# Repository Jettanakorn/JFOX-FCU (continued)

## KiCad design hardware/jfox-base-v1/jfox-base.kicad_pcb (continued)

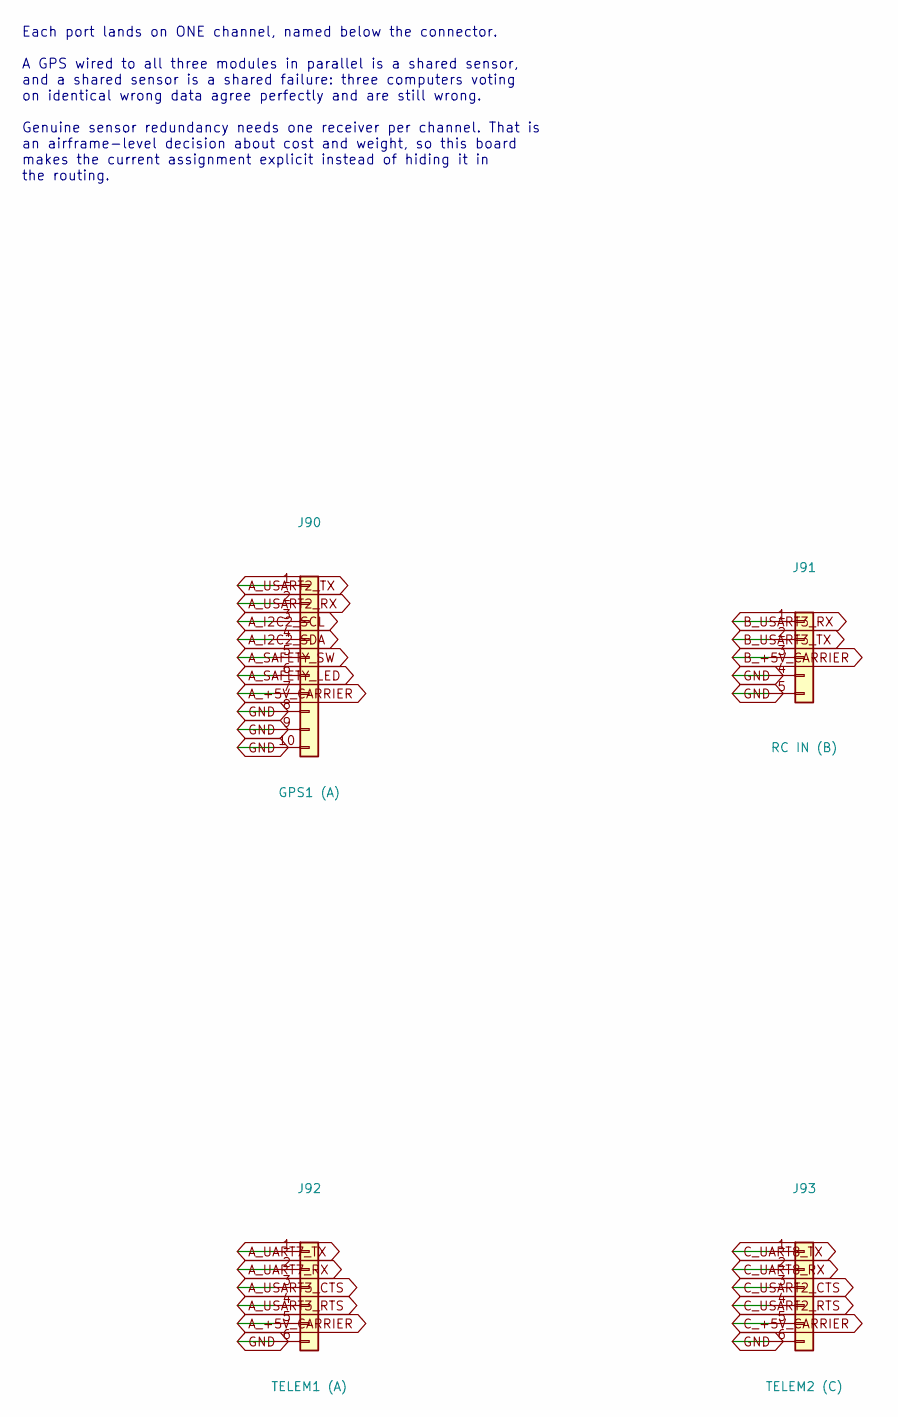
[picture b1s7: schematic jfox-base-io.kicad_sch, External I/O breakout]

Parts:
J90: GPS1 (A); JST_GH_SM10B-GHS-TB_1x10-1MP_P1.25mm_Horizontal
J91: RC IN (B); JST_GH_SM05B-GHS-TB_1x05-1MP_P1.25mm_Horizontal
J92: TELEM1 (A); JST_GH_SM06B-GHS-TB_1x06-1MP_P1.25mm_Horizontal
J93: TELEM2 (C); JST_GH_SM06B-GHS-TB_1x06-1MP_P1.25mm_Horizontal

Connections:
A_+5V_CARRIER: J90.7, J92.5; also elsewhere on the board
A_I2C2_SCL: J90.3; also elsewhere on the board
A_I2C2_SDA: J90.4; also elsewhere on the board
A_SAFETY_LED: J90.6; also elsewhere on the board
A_SAFETY_SW: J90.5; also elsewhere on the board
A_UART7_RX: J92.2; also elsewhere on the board
A_UART7_TX: J92.1; also elsewhere on the board
A_USART2_RX: J90.2; also elsewhere on the board
A_USART2_TX: J90.1; also elsewhere on the board
A_USART3_CTS: J92.3; also elsewhere on the board
A_USART3_RTS: J92.4; also elsewhere on the board
B_+5V_CARRIER: J91.3; also elsewhere on the board
B_USART3_RX: J91.1; also elsewhere on the board
B_USART3_TX: J91.2; also elsewhere on the board
C_+5V_CARRIER: J93.5; also elsewhere on the board
C_UART8_RX: J93.2; also elsewhere on the board
C_UART8_TX: J93.1; also elsewhere on the board
C_USART2_CTS: J93.3; also elsewhere on the board
C_USART2_RTS: J93.4; also elsewhere on the board
GND: J90.8, J90.9, J90.10, J91.4, J91.5, J92.6, J93.6; also elsewhere on the board

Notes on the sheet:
Each port lands on ONE channel, named below the connector. A GPS wired to all three modules in parallel is a shared sensor, and a shared sensor is a shared failure: three computers voting on identical wrong data agree perfectly and are still wrong. Genuine sensor redundancy needs one receiver per c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

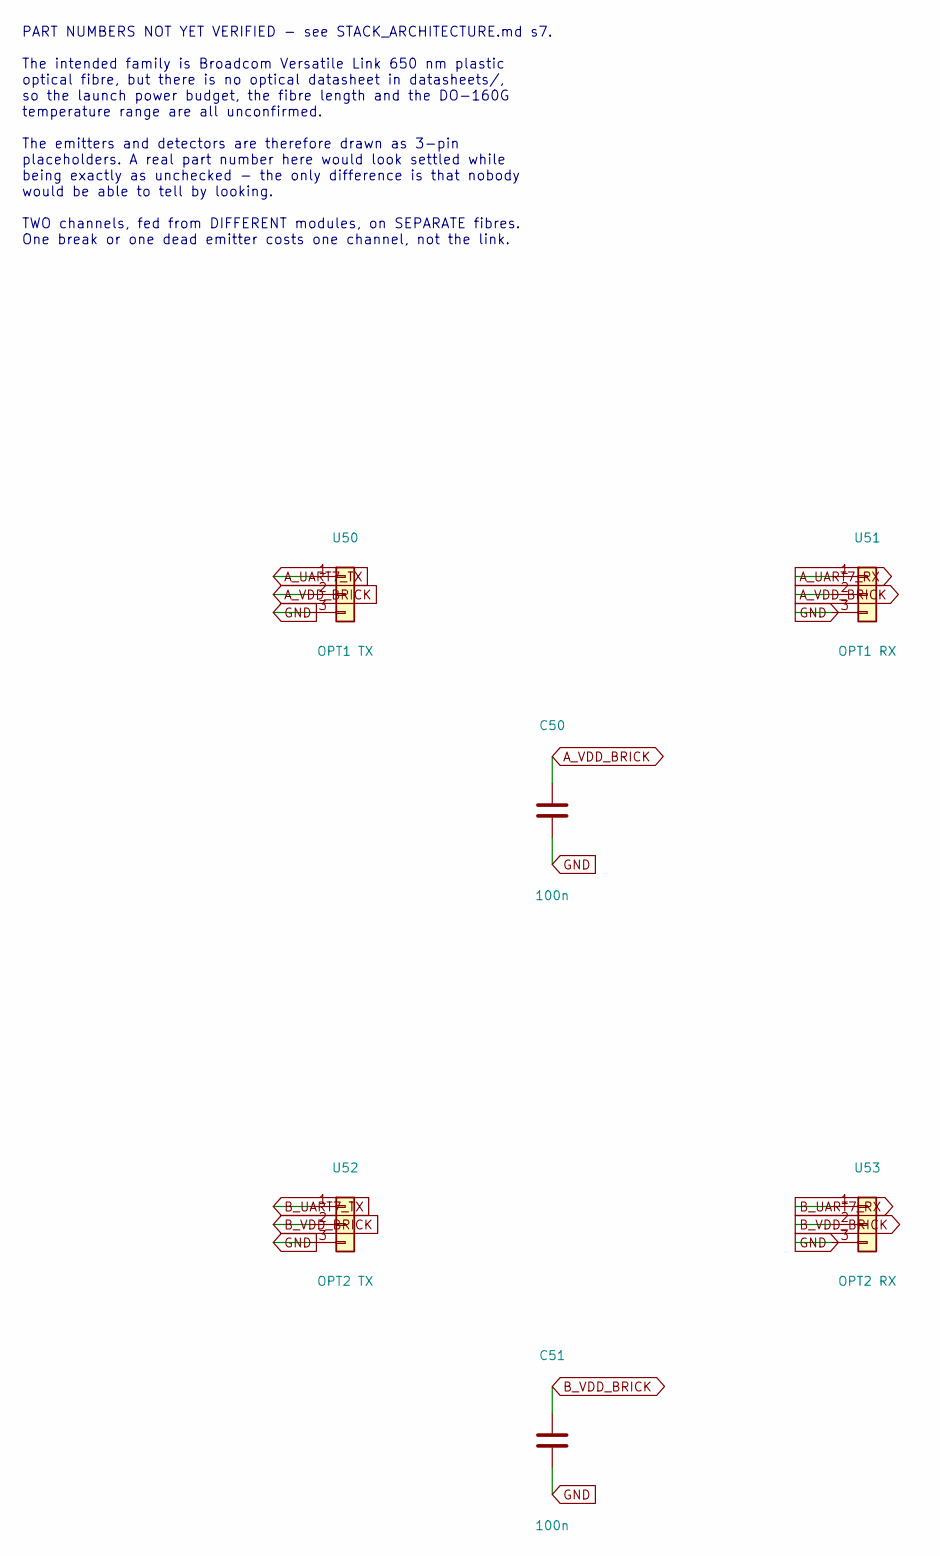
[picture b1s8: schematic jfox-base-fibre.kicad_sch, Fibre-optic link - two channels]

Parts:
C50, C51: 100n; C_0402_1005Metric
U50: OPT1 TX; AGILENT_HFBR-152x
U51: OPT1 RX; AGILENT_HFBR-252x
U52: OPT2 TX; AGILENT_HFBR-152x
U53: OPT2 RX; AGILENT_HFBR-252x

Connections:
A_UART7_RX: U51.1; also elsewhere on the board
A_UART7_TX: U50.1; also elsewhere on the board
A_VDD_BRICK: C50.1, U50.2, U51.2
B_UART7_RX: U53.1; also elsewhere on the board
B_UART7_TX: U52.1; also elsewhere on the board
B_VDD_BRICK: C51.1, U52.2, U53.2
GND: C50.2, C51.2, U50.3, U51.3, U52.3, U53.3; also elsewhere on the board

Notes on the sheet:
PART NUMBERS NOT YET VERIFIED - see STACK_ARCHITECTURE.md s7. The intended family is Broadcom Versatile Link 650 nm plastic optical fibre, but there is no optical datasheet in datasheets/, so the launch power budget, the fibre length and the DO-160G temperature range are all unconfirmed. The emitte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

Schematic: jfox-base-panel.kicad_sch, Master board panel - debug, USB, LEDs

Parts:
D1, D2, D3: GRN; LED_0805_2012Metric
J52: DEBUG; JST_GH_SM06B-GHS-TB_1x06-1MP_P1.25mm_Horizontal
J54: USB-C; JST_GH_SM05B-GHS-TB_1x05-1MP_P1.25mm_Horizontal
R60, R61, R62: 1k; R_0402_1005Metric

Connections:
A_LED_A: D1.1 (K), R60.2
A_SAFETY_LED: R60.1; also elsewhere on the board
A_SPI5_MISO: J52.2; also elsewhere on the board
A_SPI5_MOSI: J52.3; also elsewhere on the board
A_SPI5_SCK: J52.1; also elsewhere on the board
A_UART4_RX: J52.5; also elsewhere on the board
A_UART4_TX: J52.4; also elsewhere on the board
A_USART2_CTS: J54.3; also elsewhere on the board
A_USART2_RTS: J54.4; also elsewhere on the board
A_USART2_RX: J54.2; also elsewhere on the board
A_USART2_TX: J54.1; also elsewhere on the board
B_LED_A: D2.1 (K), R61.2
B_SAFETY_LED: R61.1; also elsewhere on the board
C_LED_A: D3.1 (K), R62.2
C_SAFETY_LED: R62.1; also elsewhere on the board
GND: D1.2 (A), D2.2 (A), D3.2 (A), J52.6, J54.5; also elsewhere on the board

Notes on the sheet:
One debug port and one console for the SET, on the master board. Three LEDs, one per channel, each driven from ITS OWN module. A single LED driven from a summary signal tells you the summary logic is alive, which is not the question anyone is asking when they look at it. With the lid on, these are 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

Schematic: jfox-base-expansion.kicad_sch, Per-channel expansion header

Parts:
J100: EXP A; PinHeader_2x10_P1.27mm_Vertical_SMD
J101: EXP B; PinHeader_2x10_P1.27mm_Vertical_SMD
J102: EXP C; PinHeader_2x10_P1.27mm_Vertical_SMD

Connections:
A_KEY: J100.5
A_NRST: J100.3; also elsewhere on the board
A_SWCLK: J100.2; also elsewhere on the board
A_SWDIO: J100.1; also elsewhere on the board
A_UART8_RX: J100.8; also elsewhere on the board
A_UART8_TX: J100.9; also elsewhere on the board
A_USART1_RX: J100.10; also elsewhere on the board
A_USART1_TX: J100.4; also elsewhere on the board
A_USART3_RX: J100.7; also elsewhere on the board
A_USART3_TX: J100.6; also elsewhere on the board
B_I2C2_SCL: J101.14; also elsewhere on the board
B_I2C2_SDA: J101.15; also elsewhere on the board
B_KEY: J101.5
B_NRST: J101.3; also elsewhere on the board
B_SAFETY_SW: J101.18; also elsewhere on the board
B_SPI5_MISO: J101.20; also elsewhere on the board
B_SPI5_SCK: J101.19; also elsewhere on the board
B_SWCLK: J101.2; also elsewhere on the board
B_SWDIO: J101.1; also elsewhere on the board
B_UART4_RX: J101.13; also elsewhere on the board
B_UART4_TX: J101.12; also elsewhere on the board
B_UART8_RX: J101.16; also elsewhere on the board
B_UART8_TX: J101.17; also elsewhere on the board
B_USART1_TX: J101.4; also elsewhere on the board
B_USART2_CTS: J101.8; also elsewhere on the board
B_USART2_RTS: J101.9; also elsewhere on the board
B_USART2_RX: J101.7; also elsewhere on the board
B_USART2_TX: J101.6; also elsewhere on the board
B_USART3_CTS: J101.10; also elsewhere on the board
B_USART3_RTS: J101.11; also elsewhere on the board
C_I2C2_SCL: J102.14; also elsewhere on the board
C_I2C2_SDA: J102.15; also elsewhere on the board
C_KEY: J102.5
C_NRST: J102.3; also elsewhere on the board
C_SAFETY_SW: J102.18; also elsewhere on the board
C_SPI5_MISO: J102.20; also elsewhere on the board
C_SPI5_SCK: J102.19; also elsewhere on the board
C_SWCLK: J102.2; also elsewhere on the board
C_SWDIO: J102.1; also elsewhere on the board
C_UART4_RX: J102.13; also elsewhere on the board
C_UART4_TX: J102.12; also elsewhere on the board
C_UART7_RX: J102.17; also elsewhere on the board
C_UART7_TX: J102.16; also elsewhere on the board
C_USART1_TX: J102.4; also elsewhere on the board
C_USART2_RX: J102.7; also elsewhere on the board
C_USART2_TX: J102.6; also elsewhere on the board
C_USART3_CTS: J102.10; also elsewhere on the board
C_USART3_RTS: J102.11; also elsewhere on the board
C_USART3_RX: J102.9; also elsewhere on the board
C_USART3_TX: J102.8; also elsewhere on the board
GND: J100.11, J100.12, J100.13, J100.14, J100.15, J100.16, J100.17, J100.18, J100.19, J100.20, J100.21, J100.22, J100.23, J100.24, J100.25, J100.26, J100.27, J100.28, J100.29, J100.30, J101.23, J101.24, J101.25, J101.26, J101.27, J101.28, J101.29, J101.30, J102.23, J102.24, J102.25, J102.26, J102.27, J102.28, J102.29, J102.30; also elsewhere on the board

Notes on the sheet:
Everything the dedicated ports did not claim. Derived from what the other sheets actually routed, not from a hand-kept list of spares - such a list goes stale the first time a port moves, and the symptom is a pin connected to nothing. The three headers carry DIFFERENT signals: each channel owns dif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

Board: 8 copper layers, 71 parts (22 on the bottom side), 134 nets, no tracks yet.

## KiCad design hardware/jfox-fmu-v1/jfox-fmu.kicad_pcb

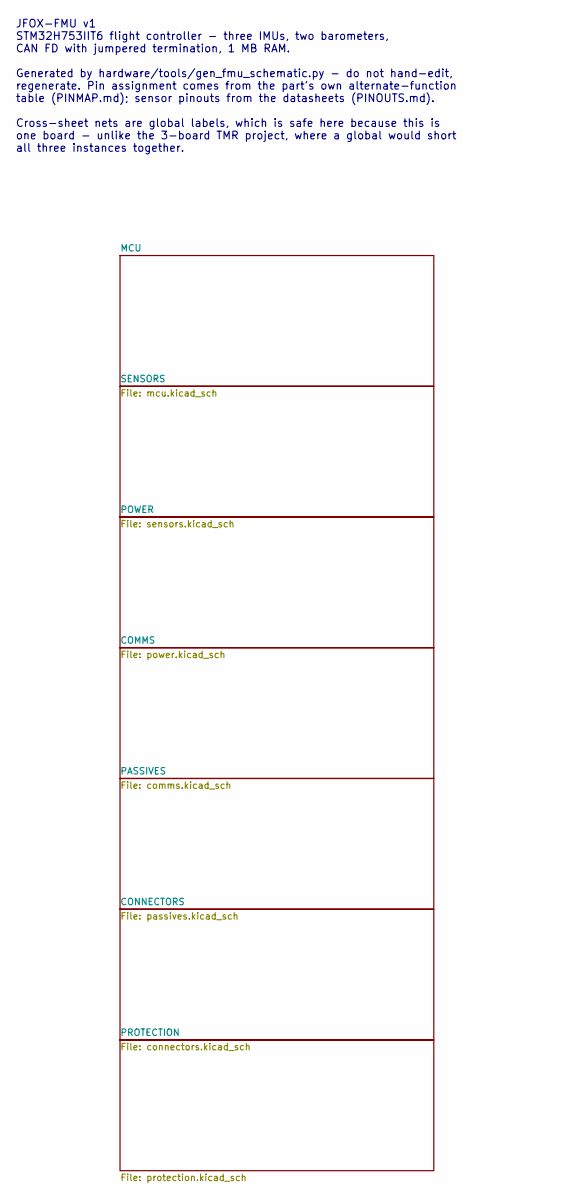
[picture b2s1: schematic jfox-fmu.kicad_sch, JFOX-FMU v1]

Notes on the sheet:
JFOX-FMU v1 STM32H753IIT6 flight controller - three IMUs, two barometers, CAN FD with jumpered termination, 1 MB RAM. Generated by hardware/tools/gen_fmu_schematic.py - do not hand-edit, regenerate. Pin assignment comes from the part's own alternate-function table (PINMAP.md); sensor pinouts from t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

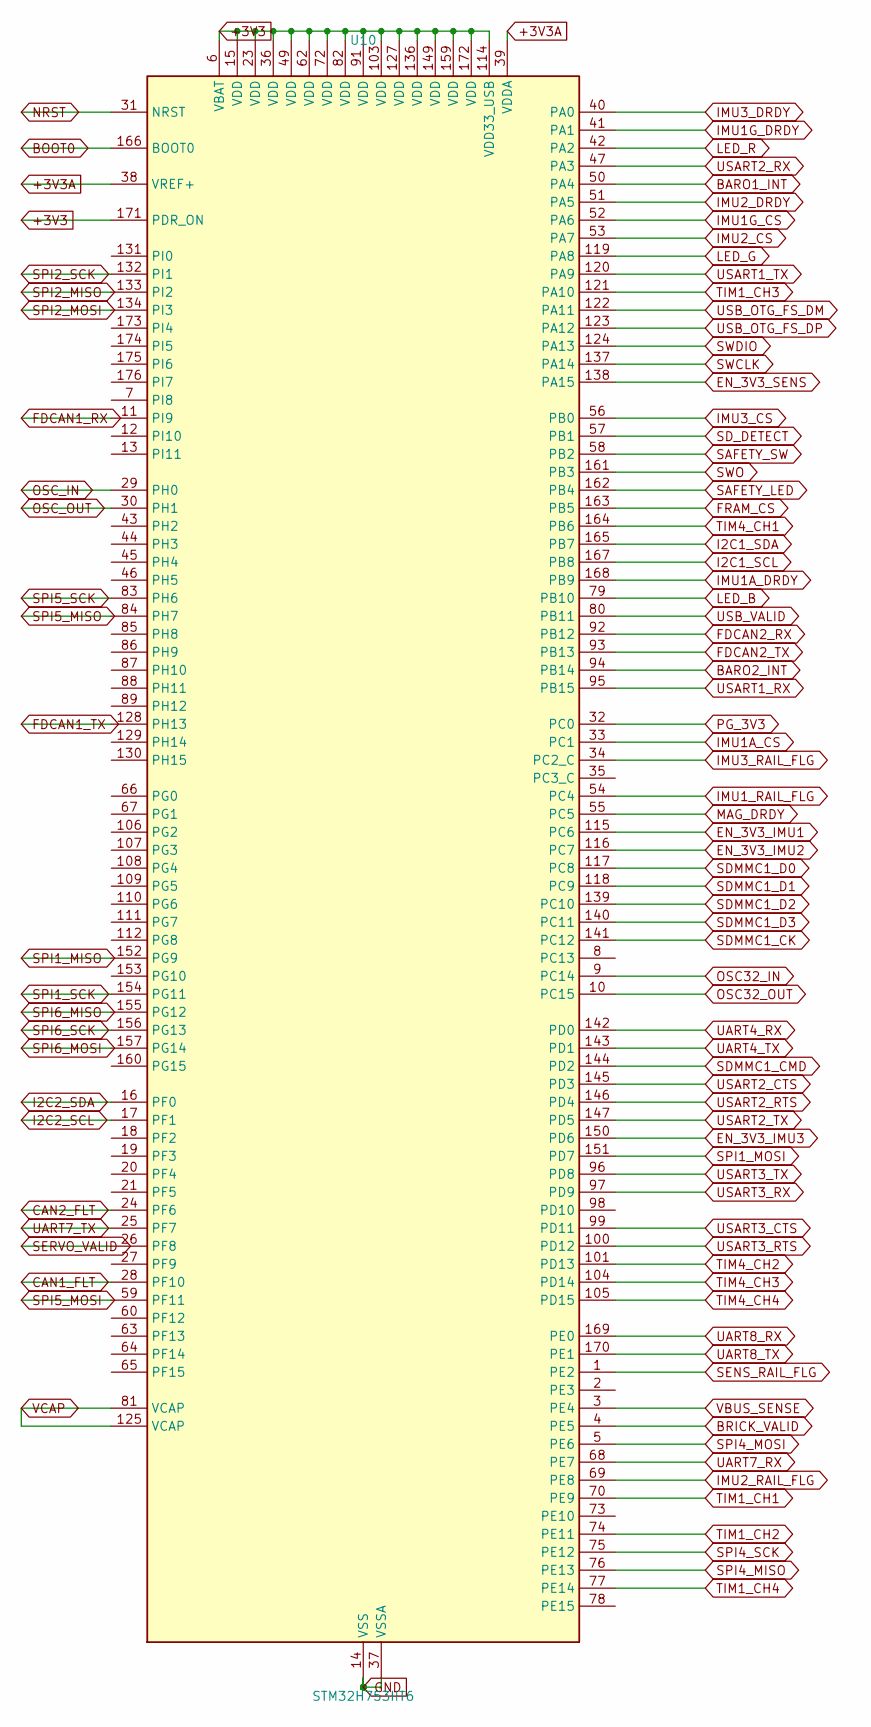
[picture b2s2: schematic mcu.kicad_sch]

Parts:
U10: STM32H753IIT6; LQFP-176_24x24mm_P0.5mm

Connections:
+3V3: U10.6 (VBAT), U10.15 (VDD), U10.23 (VDD), U10.36 (VDD), U10.49 (VDD), U10.62 (VDD), U10.72 (VDD), U10.82 (VDD), U10.91 (VDD), U10.103 (VDD), U10.114 (VDD33_USB), U10.127 (VDD), U10.136 (VDD), U10.149 (VDD), U10.159 (VDD), U10.171 (PDR_ON), U10.172 (VDD); also elsewhere on the board
+3V3A: U10.38 (VREF+), U10.39 (VDDA); also elsewhere on the board
BARO1_INT: U10.50 (PA4); also elsewhere on the board
BARO2_INT: U10.94 (PB14); also elsewhere on the board
BOOT0: U10.166 (BOOT0); also elsewhere on the board
BRICK_VALID: U10.4 (PE5)
CAN1_FLT: U10.28 (PF10); also elsewhere on the board
CAN2_FLT: U10.24 (PF6); also elsewhere on the board
EN_3V3_IMU1: U10.115 (PC6); also elsewhere on the board
EN_3V3_IMU2: U10.116 (PC7); also elsewhere on the board
EN_3V3_IMU3: U10.150 (PD6); also elsewhere on the board
EN_3V3_SENS: U10.138 (PA15); also elsewhere on the board
FDCAN1_RX: U10.11 (PI9); also elsewhere on the board
FDCAN1_TX: U10.128 (PH13); also elsewhere on the board
FDCAN2_RX: U10.92 (PB12); also elsewhere on the board
FDCAN2_TX: U10.93 (PB13); also elsewhere on the board
FRAM_CS: U10.163 (PB5); also elsewhere on the board
GND: U10.14 (VSS), U10.22 (VSS), U10.37 (VSSA), U10.48 (VSS), U10.61 (VSS), U10.71 (VSS), U10.90 (VSS), U10.102 (VSS), U10.113 (VSS), U10.126 (VSS), U10.135 (VSS), U10.148 (VSS), U10.158 (VSS); also elsewhere on the board
I2C1_SCL: U10.167 (PB8); also elsewhere on the board
I2C1_SDA: U10.165 (PB7); also elsewhere on the board
I2C2_SCL: U10.17 (PF1); also elsewhere on the board
I2C2_SDA: U10.16 (PF0); also elsewhere on the board
IMU1A_CS: U10.33 (PC1); also elsewhere on the board
IMU1A_DRDY: U10.168 (PB9); also elsewhere on the board
IMU1G_CS: U10.52 (PA6); also elsewhere on the board
IMU1G_DRDY: U10.41 (PA1); also elsewhere on the board
IMU1_RAIL_FLG: U10.54 (PC4); also elsewhere on the board
IMU2_CS: U10.53 (PA7); also elsewhere on the board
IMU2_DRDY: U10.51 (PA5); also elsewhere on the board
IMU2_RAIL_FLG: U10.69 (PE8); also elsewhere on the board
IMU3_CS: U10.56 (PB0); also elsewhere on the board
IMU3_DRDY: U10.40 (PA0); also elsewhere on the board
IMU3_RAIL_FLG: U10.34 (PC2_C); also elsewhere on the board
LED_B: U10.79 (PB10); also elsewhere on the board
LED_G: U10.119 (PA8); also elsewhere on the board
LED_R: U10.42 (PA2)
MAG_DRDY: U10.55 (PC5); also elsewhere on the board
NRST: U10.31 (NRST); also elsewhere on the board
OSC32_IN: U10.9 (PC14); also elsewhere on the board
OSC32_OUT: U10.10 (PC15); also elsewhere on the board
OSC_IN: U10.29 (PH0); also elsewhere on the board
OSC_OUT: U10.30 (PH1); also elsewhere on the board
PG_3V3: U10.32 (PC0); also elsewhere on the board
SAFETY_LED: U10.162 (PB4); also elsewhere on the board
SAFETY_SW: U10.58 (PB2); also elsewhere on the board
SDMMC1_CK: U10.141 (PC12); also elsewhere on the board
SDMMC1_CMD: U10.144 (PD2); also elsewhere on the board
SDMMC1_D0: U10.117 (PC8); also elsewhere on the board
SDMMC1_D1: U10.118 (PC9); also elsewhere on the board
SDMMC1_D2: U10.139 (PC10); also elsewhere on the board
SDMMC1_D3: U10.140 (PC11); also elsewhere on the board
SD_DETECT: U10.57 (PB1); also elsewhere on the board
SENS_RAIL_FLG: U10.1 (PE2); also elsewhere on the board
SERVO_VALID: U10.26 (PF8)
SPI1_MISO: U10.152 (PG9); also elsewhere on the board
SPI1_MOSI: U10.151 (PD7); also elsewhere on the board
SPI1_SCK: U10.154 (PG11); also elsewhere on the board
SPI2_MISO: U10.133 (PI2); also elsewhere on the board
SPI2_MOSI: U10.134 (PI3); also elsewhere on the board
SPI2_SCK: U10.132 (PI1); also elsewhere on the board
SPI4_MISO: U10.76 (PE13); also elsewhere on the board
SPI4_MOSI: U10.5 (PE6); also elsewhere on the board
SPI4_SCK: U10.75 (PE12); also elsewhere on the board
SPI5_MISO: U10.84 (PH7); also elsewhere on the board
SPI5_MOSI: U10.59 (PF11); also elsewhere on the board
SPI5_SCK: U10.83 (PH6); also elsewhere on the board
SPI6_MISO: U10.155 (PG12); also elsewhere on the board
SPI6_MOSI: U10.157 (PG14); also elsewhere on the board
SPI6_SCK: U10.156 (PG13); also elsewhere on the board
SWCLK: U10.137 (PA14); also elsewhere on the board
SWDIO: U10.124 (PA13); also elsewhere on the board
SWO: U10.161 (PB3)
TIM1_CH1: U10.70 (PE9); also elsewhere on the board
TIM1_CH2: U10.74 (PE11); also elsewhere on the board
TIM1_CH3: U10.121 (PA10); also elsewhere on the board
TIM1_CH4: U10.77 (PE14); also elsewhere on the board
TIM4_CH1: U10.164 (PB6); also elsewhere on the board
TIM4_CH2: U10.101 (PD13); also elsewhere on the board
TIM4_CH3: U10.104 (PD14); also elsewhere on the board
TIM4_CH4: U10.105 (PD15); also elsewhere on the board
UART4_RX: U10.142 (PD0); also elsewhere on the board
UART4_TX: U10.143 (PD1); also elsewhere on the board
UART7_RX: U10.68 (PE7); also elsewhere on the board
UART7_TX: U10.25 (PF7); also elsewhere on the board
UART8_RX: U10.169 (PE0); also elsewhere on the board
UART8_TX: U10.170 (PE1); also elsewhere on the board
USART1_RX: U10.95 (PB15); also elsewhere on the board
USART1_TX: U10.120 (PA9); also elsewhere on the board
USART2_CTS: U10.145 (PD3); also elsewhere on the board
USART2_RTS: U10.146 (PD4); also elsewhere on the board
USART2_RX: U10.47 (PA3); also elsewhere on the board
USART2_TX: U10.147 (PD5); also elsewhere on the board
USART3_CTS: U10.99 (PD11); also elsewhere on the board
USART3_RTS: U10.100 (PD12); also elsewhere on the board
USART3_RX: U10.97 (PD9); also elsewhere on the board
USART3_TX: U10.96 (PD8); also elsewhere on the board
USB_OTG_FS_DM: U10.122 (PA11); also elsewhere on the board
USB_OTG_FS_DP: U10.123 (PA12); also elsewhere on the board
USB_VALID: U10.80 (PB11)
VBUS_SENSE: U10.3 (PE4); also elsewhere on the board
VCAP: U10.81 (VCAP), U10.125 (VCAP); also elsewhere on the board

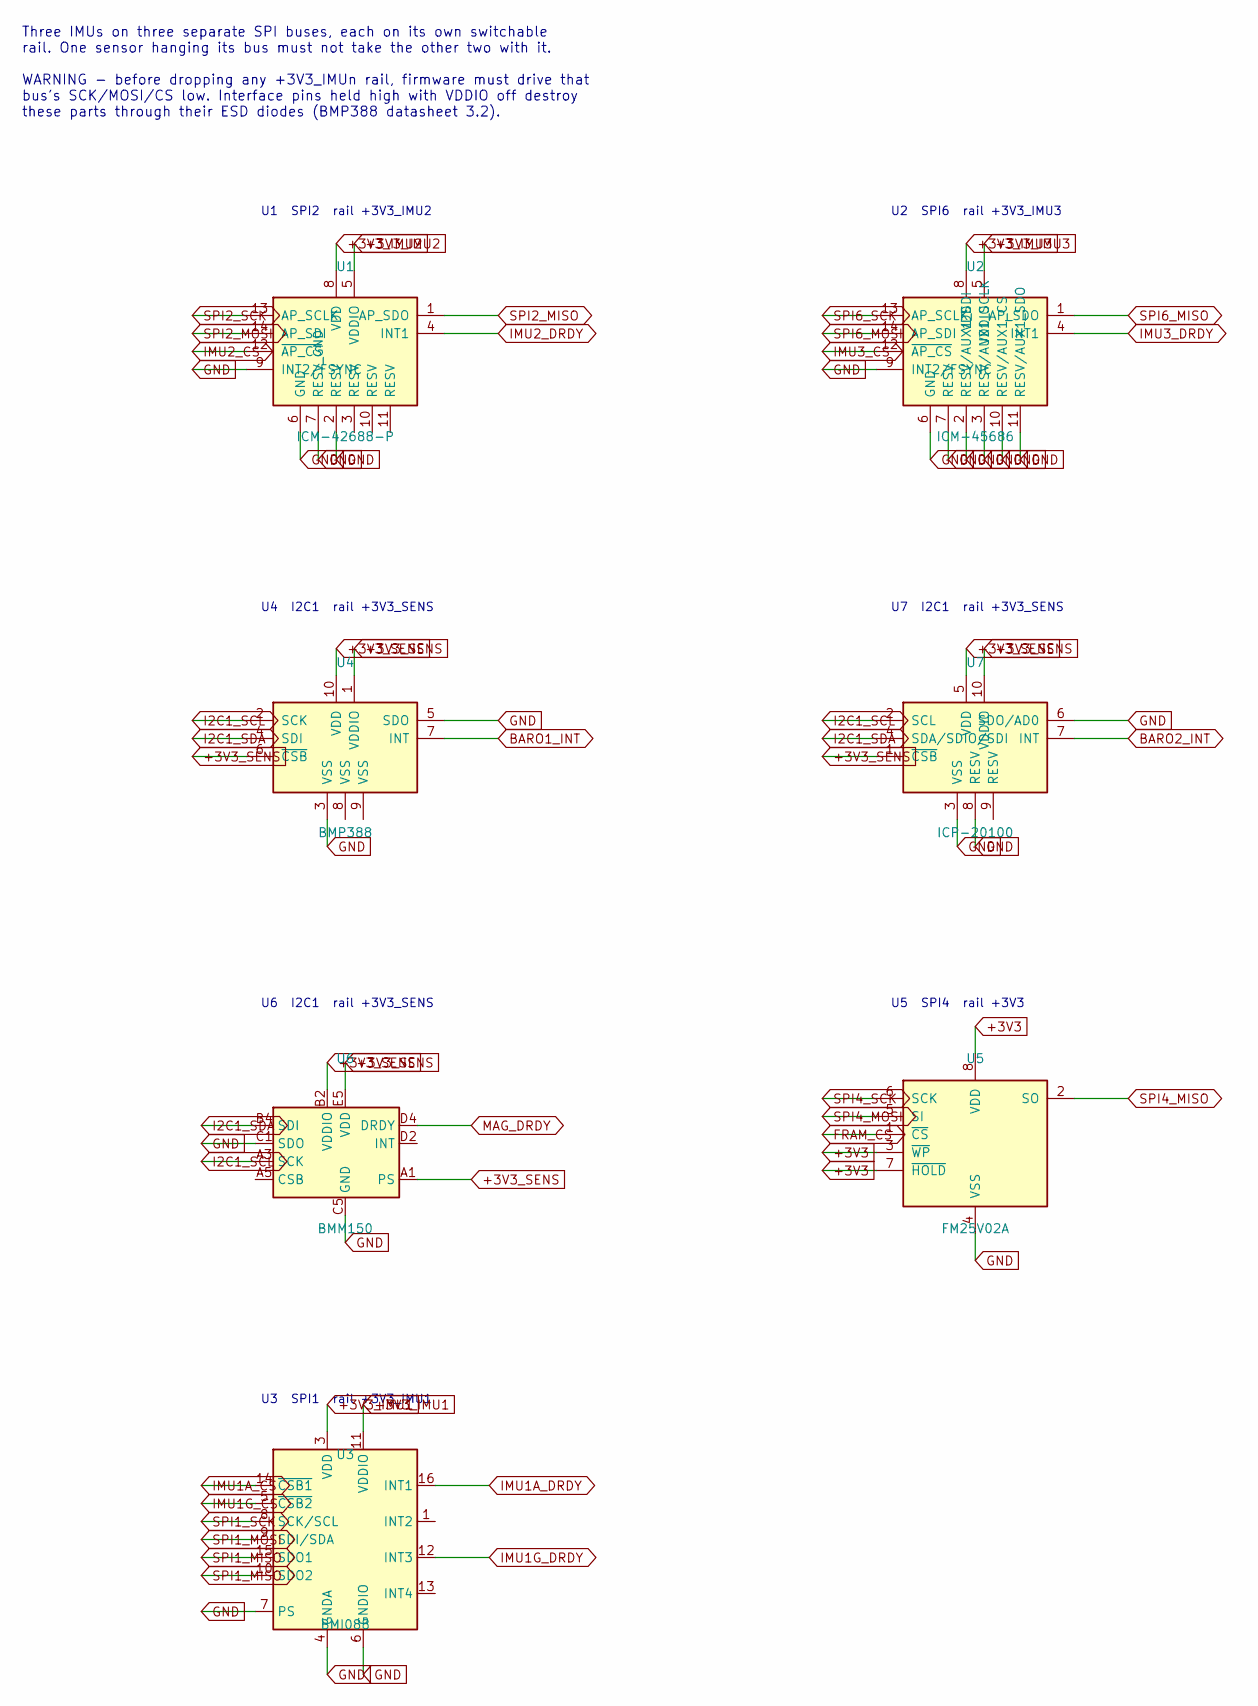
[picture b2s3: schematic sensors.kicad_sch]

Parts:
U1: ICM-42688-P; InvenSense_LGA-14_2.5x3mm_P0.5mm
U2: ICM-45686; InvenSense_LGA-14_2.5x3mm_P0.5mm
U3: BMI088; Bosch_LGA-16_4.5x3mm_P0.5mm_LayoutBorder7x1y_ClockwisePinNu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
U4: BMP388; Bosch_LGA-10_2x2mm_P0.5mm_LayoutBorder2x3y
U5: FM25V02A; SOIC-8_3.9x4.9mm_P1.27mm
U6: BMM150; WLCSP-12_1.56x1.56mm_P0.4mm
U7: ICP-20100; InvenSense_LGA-10_2x2mm_P0.5mm

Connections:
+3V3: U5.3 (~WP), U5.7 (~HOLD), U5.8 (VDD); also elsewhere on the board
+3V3_IMU1: U3.3 (VDD), U3.11 (VDDIO); also elsewhere on the board
+3V3_IMU2: U1.5 (VDDIO), U1.8 (VDD); also elsewhere on the board
+3V3_IMU3: U2.5 (VDDIO), U2.8 (VDD); also elsewhere on the board
+3V3_SENS: U4.1 (VDDIO), U4.6 (~CSB), U4.10 (VDD), U6.A1 (PS), U6.B2 (VDDIO), U6.E5 (VDD), U7.1 (~CSB), U7.5 (VDD), U7.10 (VDDIO); also elsewhere on the board
BARO1_INT: U4.7 (INT); also elsewhere on the board
BARO2_INT: U7.7 (INT); also elsewhere on the board
FRAM_CS: U5.1 (~CS); also elsewhere on the board
GND: U1.2 (RESV), U1.6 (GND), U1.7 (RESV_GND), U1.9 (INT2/FSYNC), U2.2 (RESV/AUX1_SDI), U2.3 (RESV/AUX1_SCLK), U2.6 (GND), U2.7 (RESV), U2.9 (INT2/FSYNC), U2.10 (RESV/AUX1_CS), U2.11 (RESV/AUX1_SDO), U3.2 (GNDA), U3.4 (GNDA), U3.6 (GNDIO), U3.7 (PS), U4.3 (VSS), U4.5 (SDO), U5.4 (VSS), U6.C1 (SDO), U6.C5 (GND), U6.E1 (GND), U6.E3 (GND), U7.3 (VSS), U7.6 (SDO/AD0), U7.8 (RESV); also elsewhere on the board
I2C1_SCL: U4.2 (SCK), U6.A3 (SCK), U7.2 (SCL); also elsewhere on the board
I2C1_SDA: U4.4 (SDI), U6.B4 (SDI), U7.4 (SDA/SDIO/SDI); also elsewhere on the board
IMU1A_CS: U3.14 (~CSB1); also elsewhere on the board
IMU1A_DRDY: U3.16 (INT1); also elsewhere on the board
IMU1G_CS: U3.5 (~CSB2); also elsewhere on the board
IMU1G_DRDY: U3.12 (INT3); also elsewhere on the board
IMU2_CS: U1.12 (~AP_CS); also elsewhere on the board
IMU2_DRDY: U1.4 (INT1); also elsewhere on the board
IMU3_CS: U2.12 (~AP_CS); also elsewhere on the board
IMU3_DRDY: U2.4 (INT1); also elsewhere on the board
MAG_DRDY: U6.D4 (DRDY); also elsewhere on the board
SPI1_MISO: U3.10 (SDO2), U3.15 (SDO1); also elsewhere on the board
SPI1_MOSI: U3.9 (SDI/SDA); also elsewhere on the board
SPI1_SCK: U3.8 (SCK/SCL); also elsewhere on the board
SPI2_MISO: U1.1 (AP_SDO); also elsewhere on the board
SPI2_MOSI: U1.14 (AP_SDI); also elsewhere on the board
SPI2_SCK: U1.13 (AP_SCLK); also elsewhere on the board
SPI4_MISO: U5.2 (SO); also elsewhere on the board
SPI4_MOSI: U5.5 (SI); also elsewhere on the board
SPI4_SCK: U5.6 (SCK); also elsewhere on the board
SPI6_MISO: U2.1 (AP_SDO); also elsewhere on the board
SPI6_MOSI: U2.14 (AP_SDI); also elsewhere on the board
SPI6_SCK: U2.13 (AP_SCLK); also elsewhere on the board

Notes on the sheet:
Three IMUs on three separate SPI buses, each on its own switchable rail. One sensor hanging its bus must not take the other two with it. WARNING - before dropping any +3V3_IMUn rail, firmware must drive that bus's SCK/MOSI/CS low. Interface pins held high with VDDIO off destroy these parts through 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
U1 SPI2 rail +3V3_IMU2
U2 SPI6 rail +3V3_IMU3
U4 I2C1 rail +3V3_SENS
U7 I2C1 rail +3V3_SENS
U6 I2C1 rail +3V3_SENS
U5 SPI4 rail +3V3
U3 SPI1 rail +3V3_IMU1

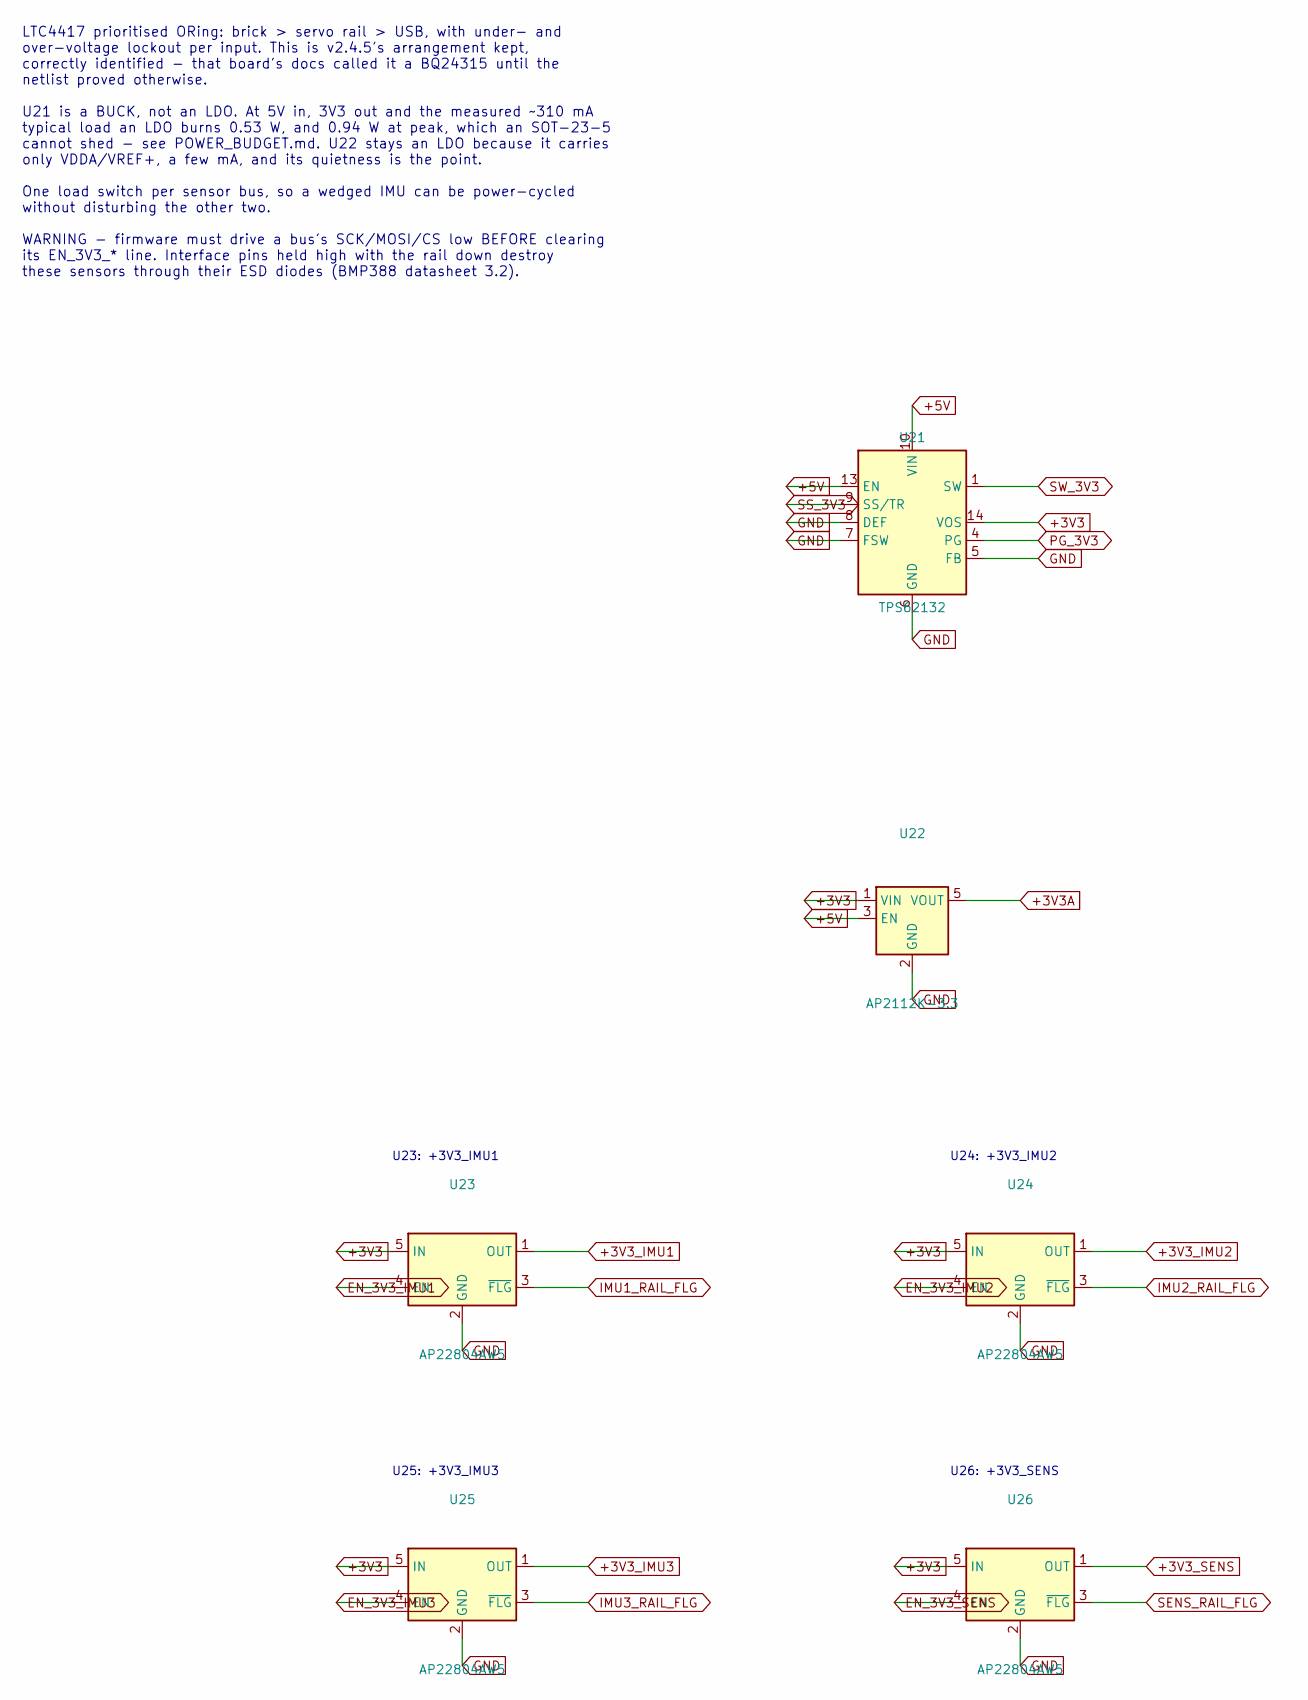
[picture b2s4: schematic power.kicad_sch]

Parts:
U21: TPS62132; VQFN-16-1EP_3x3mm_P0.5mm_EP1.6x1.6mm_ThermalVias
U22: AP2112K-3.3; SOT-23-5
U23, U24, U25, U26: AP22804AW5; SOT-23-5

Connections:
+3V3: U21.14 (VOS), U22.1 (VIN), U23.5 (IN), U24.5 (IN), U25.5 (IN), U26.5 (IN); also elsewhere on the board
+3V3A: U22.5 (VOUT); also elsewhere on the board
+3V3_IMU1: U23.1 (OUT); also elsewhere on the board
+3V3_IMU2: U24.1 (OUT); also elsewhere on the board
+3V3_IMU3: U25.1 (OUT); also elsewhere on the board
+3V3_SENS: U26.1 (OUT); also elsewhere on the board
+5V: U21.10 (VIN), U21.11 (VIN), U21.12 (VIN), U21.13 (EN), U22.3 (EN); also elsewhere on the board
EN_3V3_IMU1: U23.4 (EN); also elsewhere on the board
EN_3V3_IMU2: U24.4 (EN); also elsewhere on the board
EN_3V3_IMU3: U25.4 (EN); also elsewhere on the board
EN_3V3_SENS: U26.4 (EN); also elsewhere on the board
GND: U21.5 (FB), U21.6 (GND), U21.7 (FSW), U21.8 (DEF), U21.15 (GND), U21.16 (GND), U21.17 (GND), U22.2 (GND), U23.2 (GND), U24.2 (GND), U25.2 (GND), U26.2 (GND); also elsewhere on the board
IMU1_RAIL_FLG: U23.3 (~FLG); also elsewhere on the board
IMU2_RAIL_FLG: U24.3 (~FLG); also elsewhere on the board
IMU3_RAIL_FLG: U25.3 (~FLG); also elsewhere on the board
PG_3V3: U21.4 (PG); also elsewhere on the board
SENS_RAIL_FLG: U26.3 (~FLG); also elsewhere on the board
SS_3V3: U21.9 (SS/TR); also elsewhere on the board
SW_3V3: U21.1 (SW), U21.2 (SW), U21.3 (SW); also elsewhere on the board

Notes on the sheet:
LTC4417 prioritised ORing: brick > servo rail > USB, with under- and over-voltage lockout per input. This is v2.4.5's arrangement kept, correctly identified - that board's docs called it a BQ24315 until the netlist proved otherwise. U21 is a BUCK, not an LDO. At 5V in, 3V3 out and the measured ~310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
U23: +3V3_IMU1
U24: +3V3_IMU2
U25: +3V3_IMU3
U26: +3V3_SENS
